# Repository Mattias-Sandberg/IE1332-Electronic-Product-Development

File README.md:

# IE1332-Electronic-Product-Development
Within the Electronic-Product-Development course, I constructed a Wind down timer in KICAD and soldered the components together into board. I also wrote a scientific article about solar energy and its applications in modern society

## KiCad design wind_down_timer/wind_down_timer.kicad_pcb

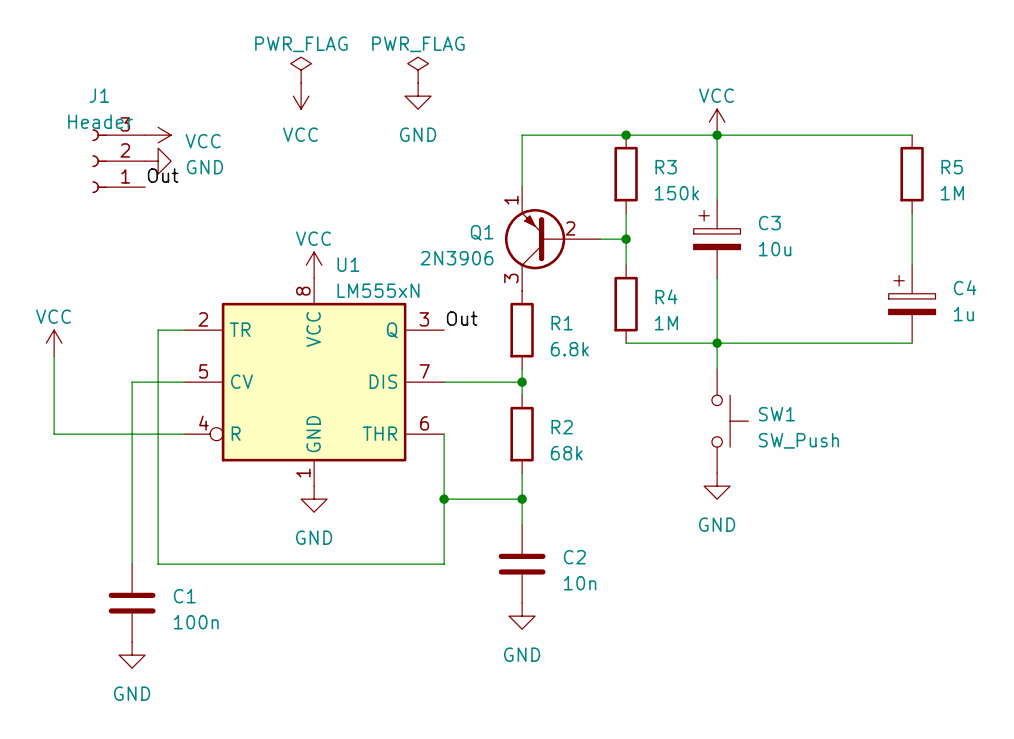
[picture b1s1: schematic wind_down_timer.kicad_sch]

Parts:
C1: 100n; C_Disc_D5.0mm_W2.5mm_P2.50mm
C2: 10n; C_Disc_D5.0mm_W2.5mm_P2.50mm
C3: 10u; CP_Radial_D5.0mm_P2.00mm
C4: 1u; CP_Radial_D5.0mm_P2.00mm
J1: Header; PinHeader_1x03_P2.54mm_Vertical
Q1: 2N3906; TO-92L_HandSolder
R1: 6.8k; R_Axial_DIN0207_L6.3mm_D2.5mm_P10.16mm_Horizontal
R2: 68k; R_Axial_DIN0207_L6.3mm_D2.5mm_P10.16mm_Horizontal
R3: 150k; R_Axial_DIN0207_L6.3mm_D2.5mm_P10.16mm_Horizontal
R4, R5: 1M; R_Axial_DIN0207_L6.3mm_D2.5mm_P10.16mm_Horizontal
SW1: SW_Push; SW_PUSH_6mm
U1: LM555xN; DIP-8_W7.62mm

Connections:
/Out: J1.1, U1.3 (Q)
GND: C1.2, C2.2, J1.2, SW1.2, U1.1 (GND)
unnamed: C3.2, C4.2, R4.2, SW1.1
unnamed: C4.1, R5.2
unnamed: Q1.2 (B), R3.2, R4.1
unnamed: Q1.3 (C), R1.1
unnamed: C1.1, U1.5 (CV)
unnamed: R1.2, R2.1, U1.7 (DIS)
unnamed: C2.1, R2.2, U1.2 (TR), U1.6 (THR)
VCC: C3.1, J1.3, Q1.1 (E), R3.1, R5.1, U1.4 (R), U1.8 (VCC)

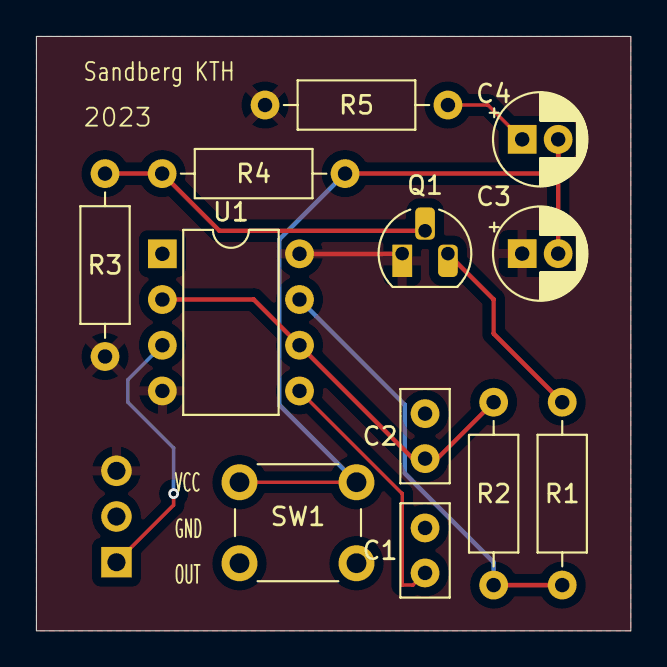
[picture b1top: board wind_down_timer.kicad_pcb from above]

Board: 2 copper layers, 33.0 x 33.0 mm, 13 parts (1 on the bottom side), 10 nets.
